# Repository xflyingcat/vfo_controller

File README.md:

# CAT VFO Controller for Xiegu G90 (STM32 + MT6701)

📺 [Youtube video: VFO controller in action](https://youtu.be/r33iY527tN8)

---
<details>
<summary><b>Читать на русском языке 🇷🇺</b></summary>

Выносной магнитный валкодер (пульт управления) для КВ-трансивера **Xiegu G90**. 

Проект разработан на базе неблокирующих конечных автоматов (FSM) для воссоздания классического «аналогового» и тактильно приятного ощущения плавной настройки, которого так не хватает штатным энкодерам.

Официальная страница проекта: [https://xflyingcat.ru/catvfoctrl.html](https://xflyingcat.ru/catvfoctrl.html)

### 🚀 Технические особенности реализации (по коду)

* **Оптимизированный тайминг (50 мс) для плавной настройки:** Опрос дельты энкодера происходит с квантом времени **50 мс**. Управляющий пакет отправляется в трансивер только при вращении вала. Это обеспечивает плавность настройки без задержек и исключает перегрузку шины CAT.
* **Магнитный энкодер (MT6701):** Высокоточный бесконтактный датчик, настроенный на фиксированные **400 событий на оборот**. При шаге 10 Гц это дает **4 кГц на оборот**.
* **Аппаратный уровень (STM32F103):** 
    * Квадратурный сигнал энкодера обрабатывается аппаратным таймером `TIM1` в 16-битном режиме.
    * Отправка САТ-команд в трансивер автоматизирована через **DMA** (`DMA1_Channel4`), что освобождает процессор от ожидания отправки байт.
    * Входящий САТ-поток принимается по прерываниям во встроенный кольцевой **FIFO-буфер емкостью 128 байт** с обеспечением атомарности операций при чтении.
* **Фильтрация эха:** На однопроводной шине CI-V контроллер автоматически отфильтровывает собственное эхо отправленных пакетов, реагируя только на входящие сообщения, адресованные мастеру (`THIS_MACHINE_ADDRESS = 0xE0`).
* **Двусторонняя синхронизация (Таймаут 500 мс):** Если ручка пульта статична более 500 мс, контроллер запрашивает текущую частоту у Xiegu G90 (команда `0x25 0x00`). Это предотвращает «скачки» частоты при ручной перестройке на самом трансивере или смене диапазона.
* **Управление шагом (10 Гц / 1 Гц):** Переключение шага происходит при длительном нажатии кнопки LOCK. При возврате с точности 1 Гц на шаг 10 Гц алгоритм автоматически выполняет математическое округление частоты до десятков (`(freq / 10) * 10`), убирая дробный «хвост».

* **Решение проблемы PTT Xiegu G90:** Трансивер не имеет стандартного нормализованного входа PTT (под простую педаль с замыканием линии на землю). Данный пульт полностью решает эту проблему: вы подключаете обычную педаль в гнездо 3.5 мм пульта, при замыкании цепи на землю контроллер переводит трансивер на передачу по шине CAT (команда 0x1C).

* **Защита от залипания PTT (Anti-Stick Watchdog):** Для линии PTT реализован таймер безопасности: при непрерывном удержании передачи более **2 минут**, контроллер принудительно отключает PTT по CAT для защиты выходного каскада трансивера от перегрева.

### 🛠 Аппаратная часть (Hardware)

* **Микроконтроллер:** STM32F103C8T6.
* **Защита цепей:** Гальваническая опторазвязка линии PTT для исключения земляных петель и TVS-супрессоры на линиях RxD/TxD CAT-интерфейса.
* **Механика:** Вал на двух подшипниках с преднатягом.
* **Корпус:** Литой алюминиевый экранированный корпус **Gainta G104** с  гермовводом (дело тут не в герметичности, просто удобный способ ввода кабеля).
* **Кабель:** 

Единый пучок длиной 0.5 м (Питание DC, CAT Jack 3.5мм(штеккер), PTT Jack 3.5мм(гнездо)), введенный через гермоввод.
* **PCB** Проект будущей печатной платы представлен в формате **KiCad**. 

### 💻 Программное обеспечение процесса разработки (Software)

* **Среда разработки:** XPack arm-none-eabi gcc, XPack windows build tools.
* **EDA:** **KiCad**.
---
</details>

<details open>
<summary><b>Read in English 🇬🇧</b></summary>

External VFO controller with magnetic encoder for the **Xiegu G90** HF transceiver based on non-blocking Finite State Machines (FSM).

This project was designed to recreate the classic, tactilely pleasant "analog" feel of smooth tuning, which stock detent encoders lack.

Project Homepage: [https://xflyingcat.ru/catvfoctrl.html](https://xflyingcat.ru/catvfoctrl.html)

### 🚀 Code Architecture

* **Smooth Tuning Response (50 ms):** Encoder delta polling occurs with **50 ms** time quantum. A CAT packet is transmitted only when a physical shaft rotation is detected. This provides absolute tuning smoothness with zero lag and prevents transceiver CAT bus overloading.
* **Magnetic Encoder (MT6701):** High-precision contactless 14-bit sensor configured for a fixed **400 events per revolution**. With a 10 Hz tuning step, this delivers **4 kHz per revolution**.
* **Hardware Level (STM32F103):** 
    * Quadrature encoder signals decoded via hardware `TIM1` timer peripheral in 16-bit mode.
    * Outgoing CAT commands handled smoothly using hardware **DMA** (`DMA1_Channel4`), bypassing CPU wait cycles.
    * Incoming CAT stream parsed via an interrupt-driven ring **FIFO buffer (128 bytes)** with atomic read operation locks.
* **Echo Filtering:** On the single-wire CI-V bus, the controller automatically filters out its own transmitted echo packets by validating the destination address (`THIS_MACHINE_ADDRESS = 0xE0`).
* **Bidirectional Sync (500 ms Timeout):** If the VFO knob is idle for >500 ms, the controller automatically polls the Xiegu G90 for its current frequency (using advanced `0x25 0x00` command). This prevents frequency "jumps" if you change bands directly on the radio.
* **Step Control (10 Hz / 1 Hz):** Step size switching is bound to a long press of the LOCK button. When returning to 10 Hz, the frequency is automatically rounded to the nearest tens of Hz (`(freq / 10) * 10`) to clean up fractional offsets.

* **Xiegu G90 Non-Normalized PTT Fix:** The stock transceiver lacks a standard, normalized PTT input for simple footswitches with ground-keying. This controller completely fixes the issue: you plug any standard pedal into the VFO's 3.5mm jack, press it and the MCU instantly triggers transmission via digital CAT commands (0x1C command).

* **Industrial Grade PTT Safety (Anti-Stick Watchdog):** The PTT line features a built-in safety watchdog: if the PTT remains engaged for more than **2 minutes**, the transmission is forcefully aborted via CAT to protect the radio's PA stage from overheating.

### 🛠 Hardware Specifications

* **MCU:** STM32F103C8T6 (Custom PCB is ready to order).
* **Circuit Protection:** Optocoupler galvanic isolation for the PTT line to break ground loops; low-capacitance TVS suppressor arrays on the CAT RxD/TxD lines.
* **Mechanics:** Custom shaft assembly utilizing dual preloaded ball bearings.
* **Enclosure:** Die-cast aluminum shielded **Gainta G104** housing.
* **Cable Assembly:** 

Integrated 0.5-meter harness (DC Power, CAT 3.5mm Jack/Plug, PTT 3.5mm Jack/Socket) routed via a cable gland.

* **PCB** is presented in **KiCad** format.

### 💻 Software Stack

* **IDE:** XPack arm-none-eabi gcc, XPack windows build tools.
* **EDA:** **KiCad**.
</details>

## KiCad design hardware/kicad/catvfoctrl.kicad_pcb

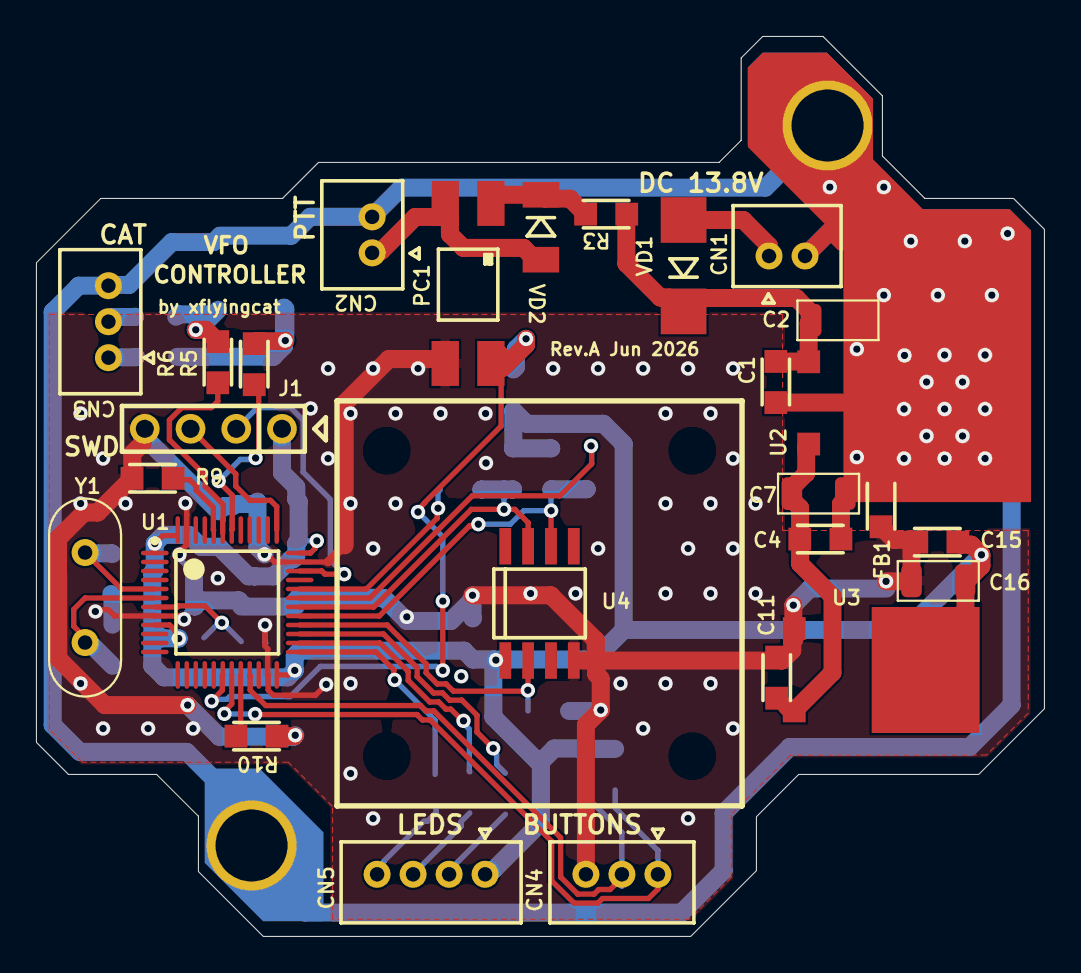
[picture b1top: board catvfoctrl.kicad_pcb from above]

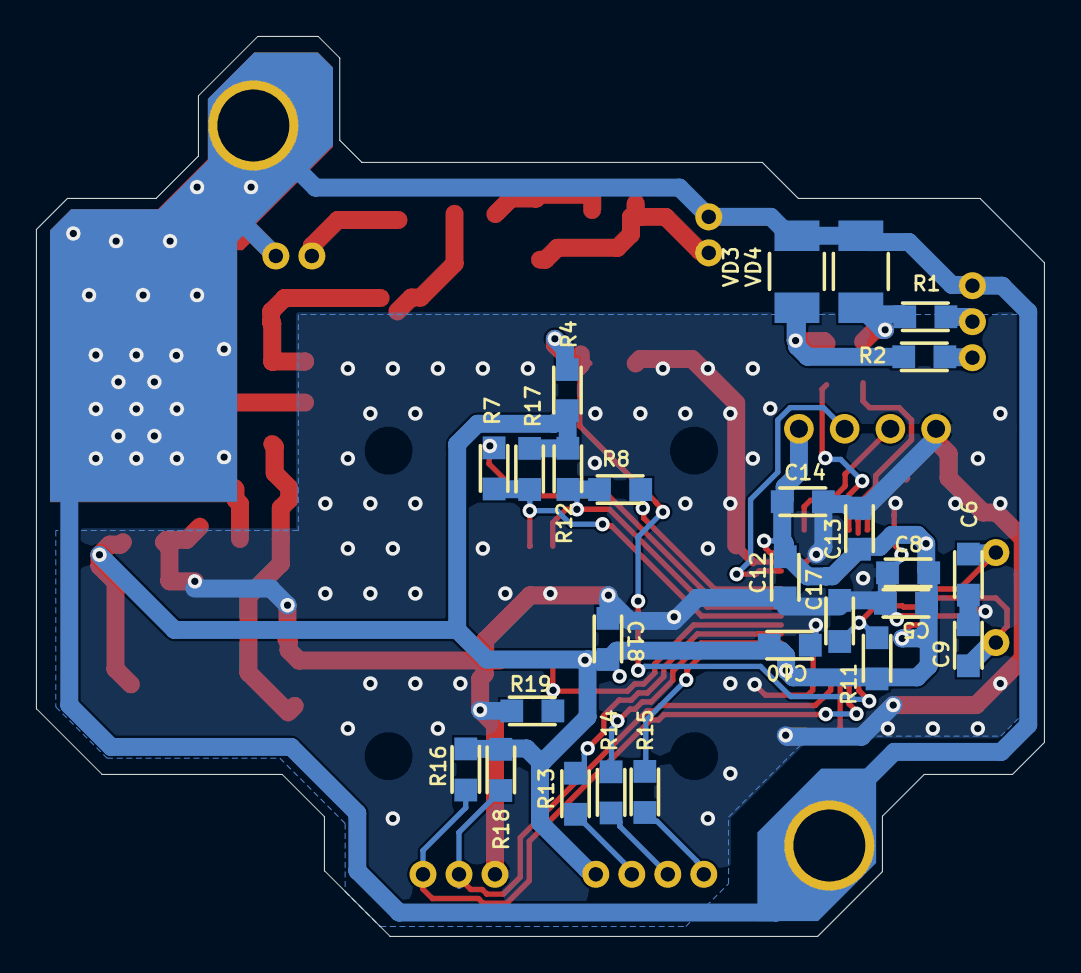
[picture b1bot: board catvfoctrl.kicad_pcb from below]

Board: 2 copper layers, 56.0 x 50.0 mm, 53 parts (26 on the bottom side), 35 nets.

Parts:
C1, C4, C5, C8, C10, C11, C12, C13, C15, C17, C18: 100N; CAP0805
C2, C7, C16: 22uF 25V; C1206
C6, C9: 22PF; CAP0805
C14: 22uF 10V; CAP0805
CN1: Power; JST2
CN2: PTT input; JST2
CN3: CAT; JST3
CN4: Buttons; JST3
CN5: LEDS; JST4
FB1: 1K/100MHZ; L0805
J1: PLS4; CON1x4
PC1: PC817XNNIP0F; P817_SMD
R1, R2, R5, R6, R7, R8: 100; RES0805
R3: 1K; RES0805
R4, R9, R10, R11, R16, R18: 10K; RES0805
R12, R17, R19: 4K7; RES0805
R13, R14, R15: 330; RES0805
U1: STM32F103C8T6; STM-LQFP48_L
U2: 78M05; SOT252
U3: LM1117-3.3V; SOT252
U4: MT6701
VD1: SK14
VD2: FDLL4148; MLL34
VD3, VD4: SMBJ5.0A-E3/52 UNIPOLAR; SMA
Y1: 8 MHz; QUARTZ_TH

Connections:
+3V3: C5.1, C8.1, C10.1, C12.1, C13.1, C14.1, C15.1, C16.1, C18.1, CN5.1, J1.1, R4.2, R11.2, R12.2, R16.2, R17.2, R18.2, U1.1, U1.9, U1.24, U1.36, U1.48, U3.3, U4.1
+5V: C4.1, C7.1, C11.1, U2.2, U3.2
BB_SCL: R8.2, U1.32
BB_SDA: R7.2, U1.31
ENCODER_A: R7.1, R17.1, U1.29, U4.6
ENCODER_B: R8.1, R12.1, U1.30, U4.7
FG: C1.2, C2.2, C4.2, C7.2, CN1.2, CN2.2, CN3.3, FB1.1, U2.3, VD3.2, VD4.2
GND: C5.2, C6.2, C8.2, C9.2, C10.2, C11.2, C12.2, C13.2, C14.2, C15.2, C16.2, C17.2, C18.2, CN4.3, FB1.2, J1.4, PC1.3, R9.1, R10.1, R19.1, U1.8, U1.23, U1.35, U1.47, U3.1, U4.4
LOCK: CN4.2, R18.1, U1.21
LOCK_LED: R14.1, U1.26
MODE: R19.2, U1.28, U4.2
NetC1_1: C1.1, C2.1, R3.1, U2.1, VD1.1
NetC6_1: C6.1, U1.5, Y1.2
NetC9_1: C9.1, U1.6, Y1.1
NetCN1_1: CN1.1, VD1.2
NetCN2_1: CN2.1, PC1.2, VD2.1
NetCN3_1: CN3.1, R2.1
NetCN3_2: CN3.2, R1.1
NetCN5_2: CN5.2, R13.2
NetCN5_3: CN5.3, R14.2
NetCN5_4: CN5.4, R15.2
NetPC1_1: PC1.1, R3.2, VD2.2
NetR1_2: R1.2, R6.1, VD4.1
NetR2_2: R2.2, R5.1, VD3.1
NetR9_2: R9.2, U1.44
NetR10_2: R10.2, U1.20
PTT: PC1.4, R4.1, U1.18
PTT_LED: R13.1, U1.27
RESET: C17.1, R11.1, U1.7
RXD: R6.2, U1.43
STEP: CN4.1, R16.1, U1.19
STEP_LED: R15.1, U1.25
SWDCLK: J1.3, U1.37
SWDIO: J1.2, U1.34
TXD: R5.2, U1.42

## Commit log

2026-06-05 Initial commit: full project with firmware, hardware and mechanics
2026-06-06 Update README: added G90 PTT fix info, YouTube demo link and refined features
2026-06-24 Added soft_i2c.c/h, mt6701.c/h for programming PPR and DIR of chip mt6701 on during startup
2026-06-26 Added Wiring Diagram, Interactive BOM and Gerber files
2026-06-26 Added Encoder_Mechanics.mp/pdf. Moved catvfoctrl_kicad_sch.pdf into hardware folder
2026-06-27 Added images for Encoder Mechanics
2026-06-28 Fixed wiring diagram
2026-06-28 Fixed README.md
